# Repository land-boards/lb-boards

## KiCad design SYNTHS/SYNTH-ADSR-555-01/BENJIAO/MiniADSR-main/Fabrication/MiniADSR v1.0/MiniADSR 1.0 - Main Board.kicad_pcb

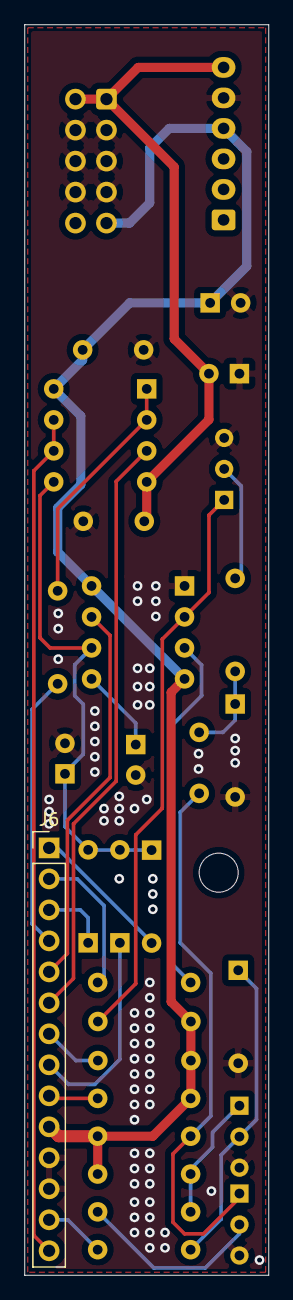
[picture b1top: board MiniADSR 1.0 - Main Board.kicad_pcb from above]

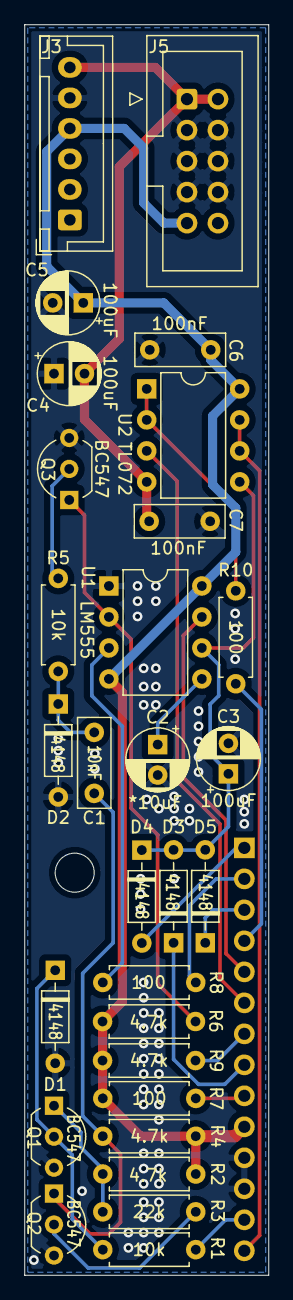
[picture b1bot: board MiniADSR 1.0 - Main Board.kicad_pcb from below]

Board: 2 copper layers, 20.0 x 102.5 mm, 30 parts (29 on the bottom side), 25 nets.

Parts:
C1: 10nF; C_Rect_L7.2mm_W2.5mm_P5.00mm_FKS2_FKP2_MKS2_MKP2
C2: *10uF; CP_Radial_D5.0mm_P2.50mm
C3, C4, C5: 100uF; CP_Radial_D5.0mm_P2.50mm
C6, C7: 100nF; C_Rect_L7.2mm_W2.5mm_P5.00mm_FKS2_FKP2_MKS2_MKP2
D1, D2, D3, D4, D5: 4148; D_DO-35_SOD27_P7.62mm_Horizontal
J3: JST_BUS; JST_XH_B6B-XH-A_1x06_P2.50mm_Vertical
J5: IDC_BUS; IDC-Header_2x05_P2.54mm_Vertical
J6: MainBoard_Pins; PinHeader_1x14_P2.54mm_Vertical
Q1, Q2, Q3: BC547; TO-92_Inline_Wide
R1, R5: 10k; R_Axial_DIN0207_L6.3mm_D2.5mm_P7.62mm_Horizontal
R2, R4, R6, R9: 4.7k; R_Axial_DIN0207_L6.3mm_D2.5mm_P7.62mm_Horizontal
R3: 22k; R_Axial_DIN0207_L6.3mm_D2.5mm_P7.62mm_Horizontal
R7, R8, R10: 100; R_Axial_DIN0207_L6.3mm_D2.5mm_P7.62mm_Horizontal
U1: LM555; DIP-8_W7.62mm
U2: TL072; DIP-8_W7.62mm

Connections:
+12V: C4.1, C6.1, J3.4, J5.9, J5.10, J6.10, R2.2, R4.2, R6.2, R7.1, R9.2, U1.4, U1.8, U2.8
-12V: C5.2, C7.2, J3.6, J5.1, J5.2, U2.4
B1: J6.13, R1.2
B2: J6.14, U2.6, U2.7
B3: D4.2, J6.1
B4: J6.2, R8.2
B5: D5.1, J6.3
B6: J6.4, R10.2
B7: J6.5, U1.7
B8: J6.6, U2.3
B9: J6.7, R9.1
B10: D3.1, J6.8
B11: J6.9, R7.2
GND2: C2.2, C3.2, C4.2, C5.1, C6.2, C7.1, D1.2, D2.2, J3.5, J5.3, J5.4, J5.5, J5.6, J5.7, J5.8, J6.11, J6.12, Q1.3, Q2.3, Q3.3, U1.1
unnamed: C1.1, D2.1, R5.1
unnamed: C1.2, Q2.1, R4.1
unnamed: C2.1, U1.5
unnamed: C3.1, D3.2, D4.1, D5.2, U1.6, U2.5
unnamed: D1.1, Q1.2, R1.1
unnamed: Q1.1, R2.1, R3.1
unnamed: Q2.2, R3.2
unnamed: Q3.1, R6.1, U1.2
unnamed: Q3.2, R5.2
unnamed: R8.1, U1.3
unnamed: R10.1, U2.1, U2.2

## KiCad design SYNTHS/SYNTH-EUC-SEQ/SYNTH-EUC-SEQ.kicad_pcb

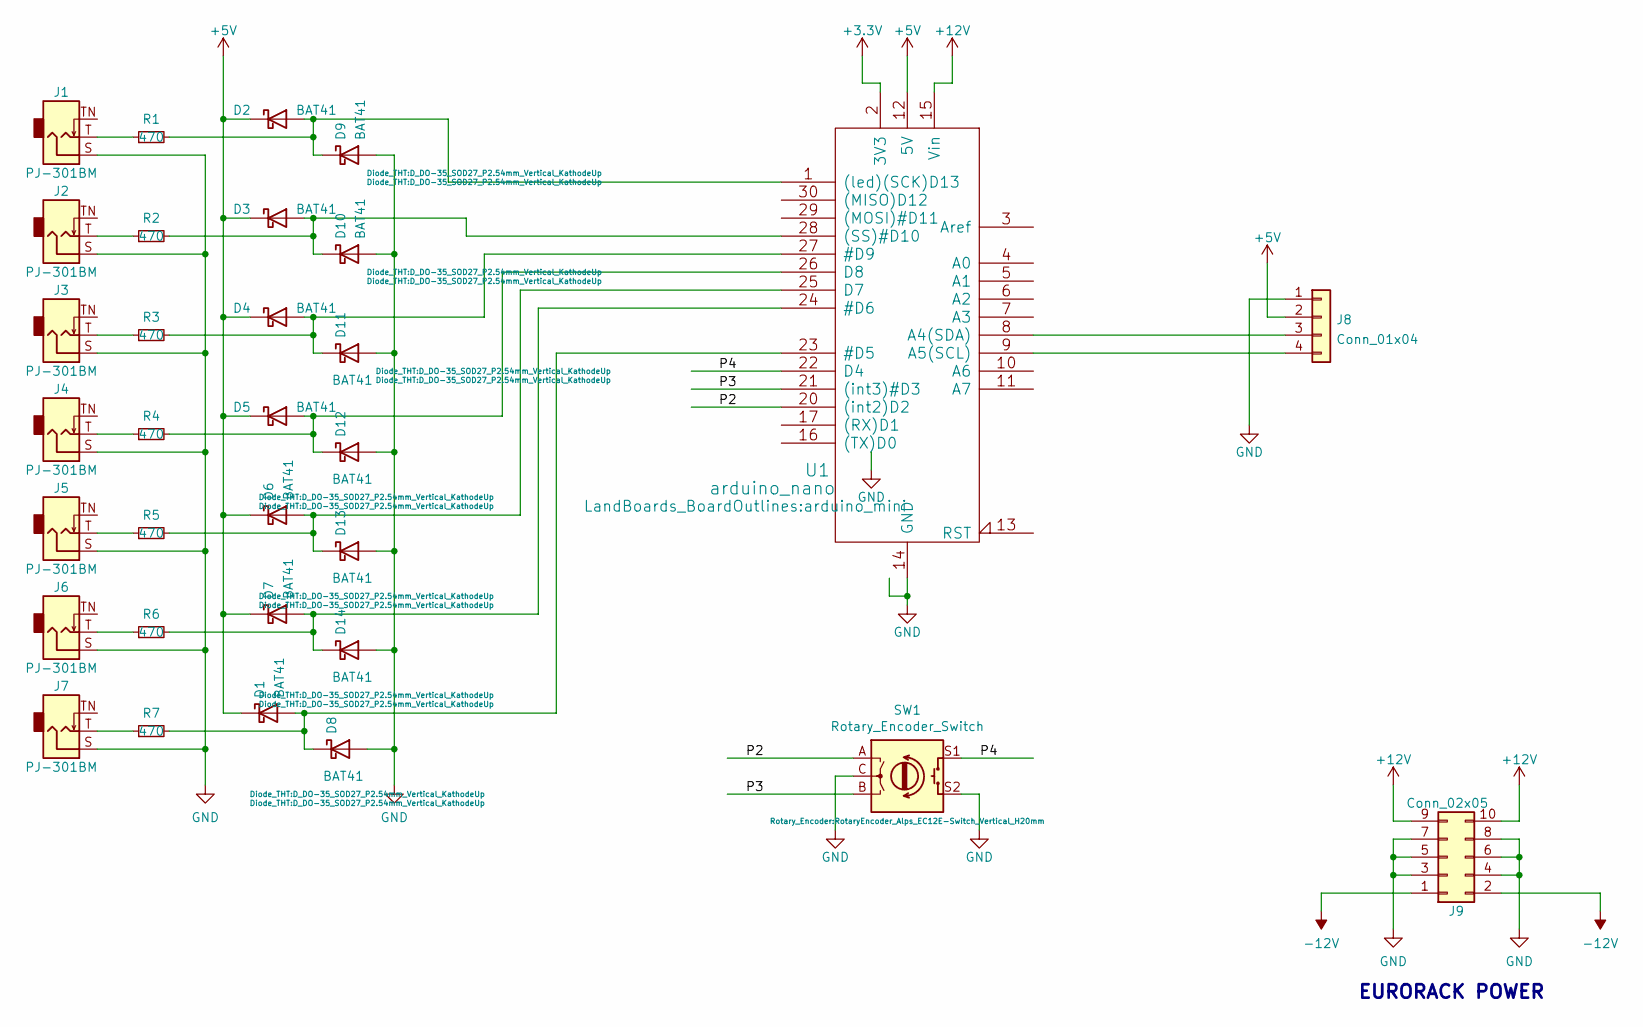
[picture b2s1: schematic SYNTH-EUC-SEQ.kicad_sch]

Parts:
D1, D2, D3, D4, D5, D6, D7, D8, D9, D10, D11, D12, D13, D14: BAT41; D_DO-35_SOD27_P2.54mm_Vertical_KathodeUp
J1, J2, J3, J4, J5, J6, J7: PJ-301BM; Jack_3.5mm_QingPu_WQP-PJ301BM_Vertical
J8: Conn_01x04; PinHeader_1x04_P2.54mm_Vertical
J9: Conn_02x05; IDC-Header_2x05_P2.54mm_Vertical
R1, R2, R3, R4, R5, R6, R7: 470; R_Axial_DIN0204_L3.6mm_D1.6mm_P2.54mm_Vertical
SW1: Rotary_Encoder_Switch; RotaryEncoder_Alps_EC12E-Switch_Vertical_H20mm
U1: arduino_nano; arduino_mini

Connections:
+3V3: U1.2 (3V3)
+5V: D1.1 (K), D2.1 (K), D3.1 (K), D4.1 (K), D5.1 (K), D6.1 (K), D7.1 (K), J8.2, U1.12 (5V)
+12V: J9.9, J9.10, U1.15 (Vin)
-12V: J9.1, J9.2
/P2: SW1.A, U1.20 ((int2)D2)
/P3: SW1.B, U1.21 ((int3)#D3)
/P4: SW1.S1, U1.22 (D4)
GND: D8.2 (A), D9.2 (A), D10.2 (A), D11.2 (A), D12.2 (A), D13.2 (A), D14.2 (A), J1.S, J2.S, J3.S, J4.S, J5.S, J6.S, J7.S, J8.1, J9.3, J9.4, J9.5, J9.6, J9.7, J9.8, SW1.C, SW1.S2, U1.14 (GND), U1.19 (GND)
unnamed: D1.2 (A), D8.1 (K), R7.2, U1.23 (#D5)
unnamed: D2.2 (A), D9.1 (K), R1.2, U1.1 ((led)(SCK)D13)
unnamed: D3.2 (A), D10.1 (K), R2.2, U1.28 ((SS)#D10)
unnamed: D4.2 (A), D11.1 (K), R3.2, U1.27 (#D9)
unnamed: D5.2 (A), D12.1 (K), R4.2, U1.26 (D8)
unnamed: D6.2 (A), D13.1 (K), R5.2, U1.25 (D7)
unnamed: D7.2 (A), D14.1 (K), R6.2, U1.24 (#D6)
unnamed: J1.T, R1.1
unnamed: J2.T, R2.1
unnamed: J3.T, R3.1
unnamed: J4.T, R4.1
unnamed: J5.T, R5.1
unnamed: J6.T, R6.1
unnamed: J7.T, R7.1
unnamed: J8.3, U1.8 (A4(SDA))
unnamed: J8.4, U1.9 (A5(SCL))

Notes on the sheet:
EURORACK POWER

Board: 2 copper layers, 32 parts (1 on the bottom side), 23 nets, no tracks yet.

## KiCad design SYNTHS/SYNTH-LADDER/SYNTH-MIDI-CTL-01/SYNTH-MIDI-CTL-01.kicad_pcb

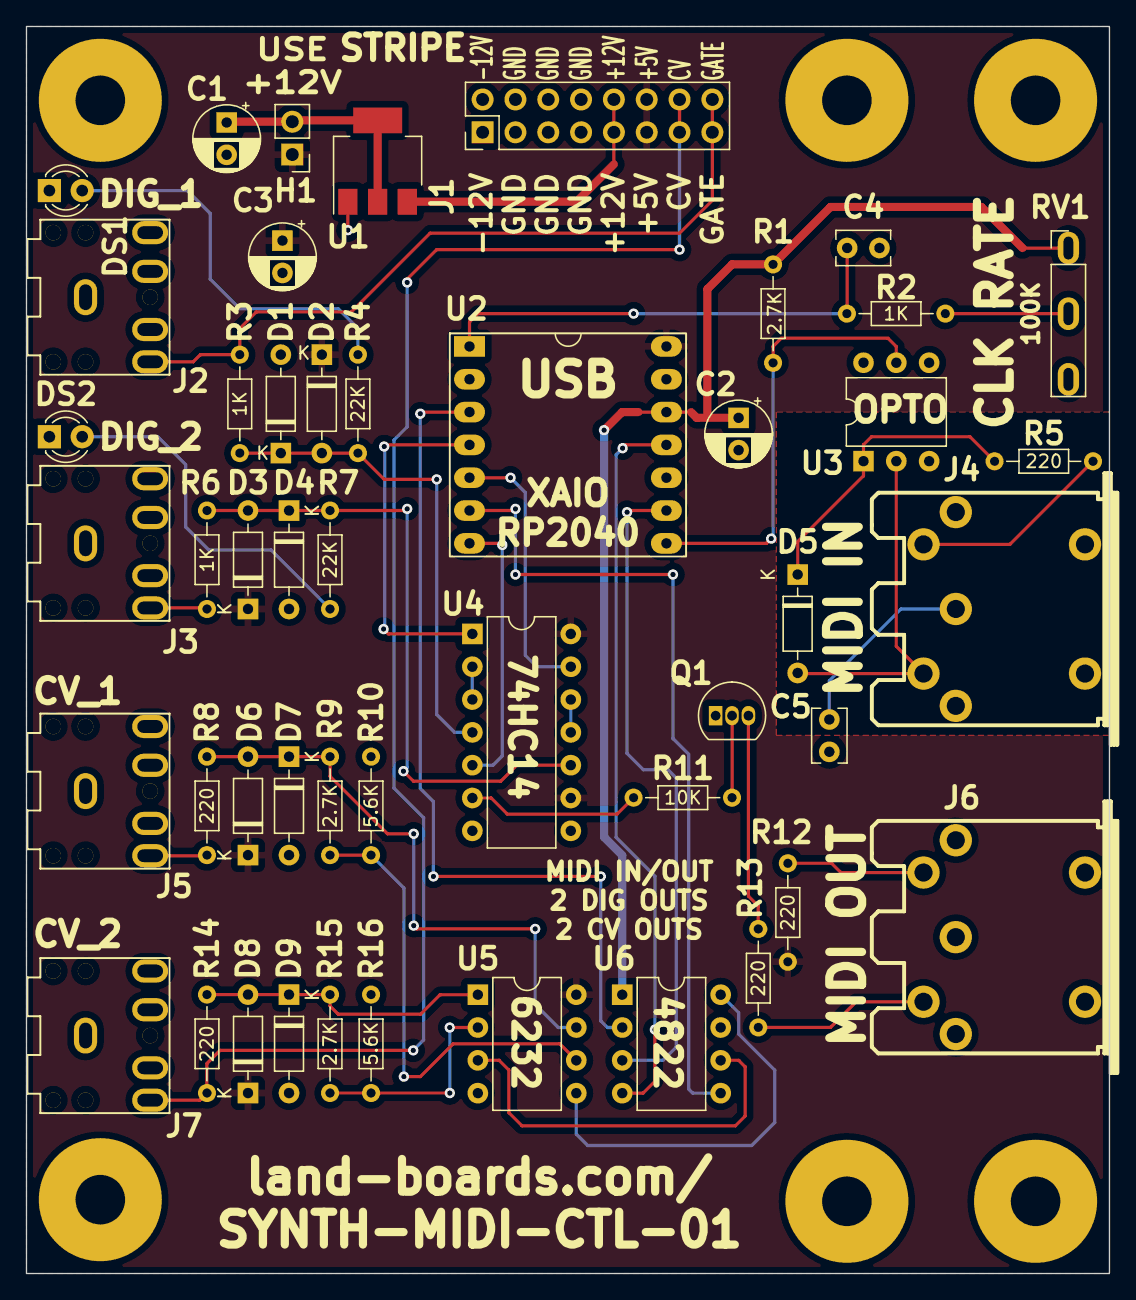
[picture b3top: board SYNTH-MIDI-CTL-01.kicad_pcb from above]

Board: 2 copper layers, 83.8 x 96.5 mm, 54 parts (0 on the bottom side), 40 nets.

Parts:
C1, C2, C3: 47uF; CP_Radial_D5.0mm_P2.50mm
C4: 220pF; C_Rect_L4.0mm_W2.5mm_P2.50mm
C5: 0.1uF; C_Rect_L4.0mm_W2.5mm_P2.50mm
D1, D2, D3, D4, D6, D7, D8, D9: BAT41; D_DO-35_SOD27_P7.62mm_Horizontal
D5: 1N914; D_DO-35_SOD27_P7.62mm_Horizontal
DS1, DS2: LED, 3mm; LED_D3.0mm
H1: HEADER, 1x2; PinHeader_1x02_P2.54mm_Vertical
J1: HEADER, SHRD, 2X8; PinHeader_2x08_P2.54mm_Vertical
J2, J3, J5, J7: AudioJack3; Jack_3.5mm_CUI_SJ1-3523N_Horizontal
J4, J6: DIN-5; MIDI_DIN-5
MTG1, MTG2, MTG3, MTG4, MTG5, MTG6: MountingHole; MTG-6-32
Q1: 2N3904; TO-92_Inline
R1, R9, R15: 2.7K; R_Axial_DIN0204_L3.6mm_D1.6mm_P7.62mm_Horizontal
R2, R3, R6: 1K; R_Axial_DIN0204_L3.6mm_D1.6mm_P7.62mm_Horizontal
R4, R7: 22K; R_Axial_DIN0204_L3.6mm_D1.6mm_P7.62mm_Horizontal
R5, R8, R12, R13, R14: 220; R_Axial_DIN0204_L3.6mm_D1.6mm_P7.62mm_Horizontal
R10, R16: 5.6K; R_Axial_DIN0204_L3.6mm_D1.6mm_P7.62mm_Horizontal
R11: 10K; R_Axial_DIN0204_L3.6mm_D1.6mm_P7.62mm_Horizontal
RV1: 100K; Pot3
U1: AZ1117H-5; SOT-223
U2: XIAO_RP2040; QT_Py
U3: CNY17-4X006; DIP-6_W7.62mm
U4: 74HC14; DIP-14_W7.62mm
U5: MCP6232; DIP-8_W7.62mm
U6: MCP4822-E/P; DIP-8_W7.62mm

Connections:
+3V3: C2.1, R1.2, RV1.1, U2.12 (3.3V), U6.1 (Vdd)
+5V: C3.1, D2.1 (K), D3.1 (K), D6.1 (K), D8.1 (K), H1.1, J1.11, J1.12, R12.2, U2.14 (5V), U4.9, U4.14 (VCC), U5.8 (VDD)
+12V: J1.9, J1.10, U1.3 (VIN)
/CLK: U2.5 (D4/SDA/P6), U4.13
/CLK_I: D3.2 (A), D4.1 (K), R6.1, R7.2, U4.10
/CV1: J5.T, R8.2
/CV2: J1.13, J1.14, J7.T, R14.2
/DIG1: J1.15, J1.16, J2.T, R3.2
/DIG2: J3.T, R6.2
/FREQ_POT: C4.1, R2.2, U2.1 (D0/P26)
/GATE: U2.4 (D3/P29), U4.1
/GATE_I: D1.1 (K), D2.2 (A), R3.1, R4.2, U4.4
/MIDI_IN: J4.4, R5.1
/RXD: R1.1, U2.8 (D7/RX/P1), U3.5
/SPI_LDAC: U2.6 (D5/SCL/P7), U6.5 (~LDAC)
/SPI_MOSI: U2.11 (D10/MOSI/P3), U6.4 (SDI)
/SPI_SCK: U2.9 (D8/SCK/P2), U6.3 (SCK)
/SPI_SS: U2.3 (D2/P28), U6.2 (~CS)
/TXD: U2.7 (D6/TX/P0), U4.5
GND: C1.2, C2.2, C3.2, C4.2, C5.2, D1.2 (A), D4.2 (A), D7.2 (A), D9.2 (A), DS1.1 (K), DS2.1 (K), J1.3, J1.4, J1.5, J1.6, J1.7, J1.8, J2.S, J3.S, J5.S, J6.2, J7.S, Q1.1 (E), R10.1, R16.1, RV1.3, U1.1 (GND), U2.13 (GND), U3.4, U4.7 (GND), U5.4 (VSS), U6.7 (Vss)
unnamed: C1.1, H1.2, U1.2 (VO), U1.4 (VO)
unnamed: C5.1, J4.2
unnamed: D5.1 (K), R5.2, U3.1
unnamed: D5.2 (A), J4.5, U3.2
unnamed: D6.2 (A), D7.1 (K), R8.1, R9.2, U5.7 (Q)
unnamed: D8.2 (A), D9.1 (K), R14.1, R15.2, U5.1 (Q)
unnamed: DS1.2 (A), R4.1
unnamed: DS2.2 (A), R7.1
unnamed: J6.4, R12.1
unnamed: J6.5, R13.2
unnamed: Q1.2 (B), R11.1
unnamed: Q1.3 (C), R13.1
unnamed: R2.1, RV1.2
unnamed: R9.1, R10.2, U5.6 (-)
unnamed: R11.2, U4.6
unnamed: R15.1, R16.2, U5.2 (-)
unnamed: U4.2, U4.3
unnamed: U4.11, U4.12
unnamed: U5.3 (+), U6.6 (VB)
unnamed: U5.5 (+), U6.8 (VA)

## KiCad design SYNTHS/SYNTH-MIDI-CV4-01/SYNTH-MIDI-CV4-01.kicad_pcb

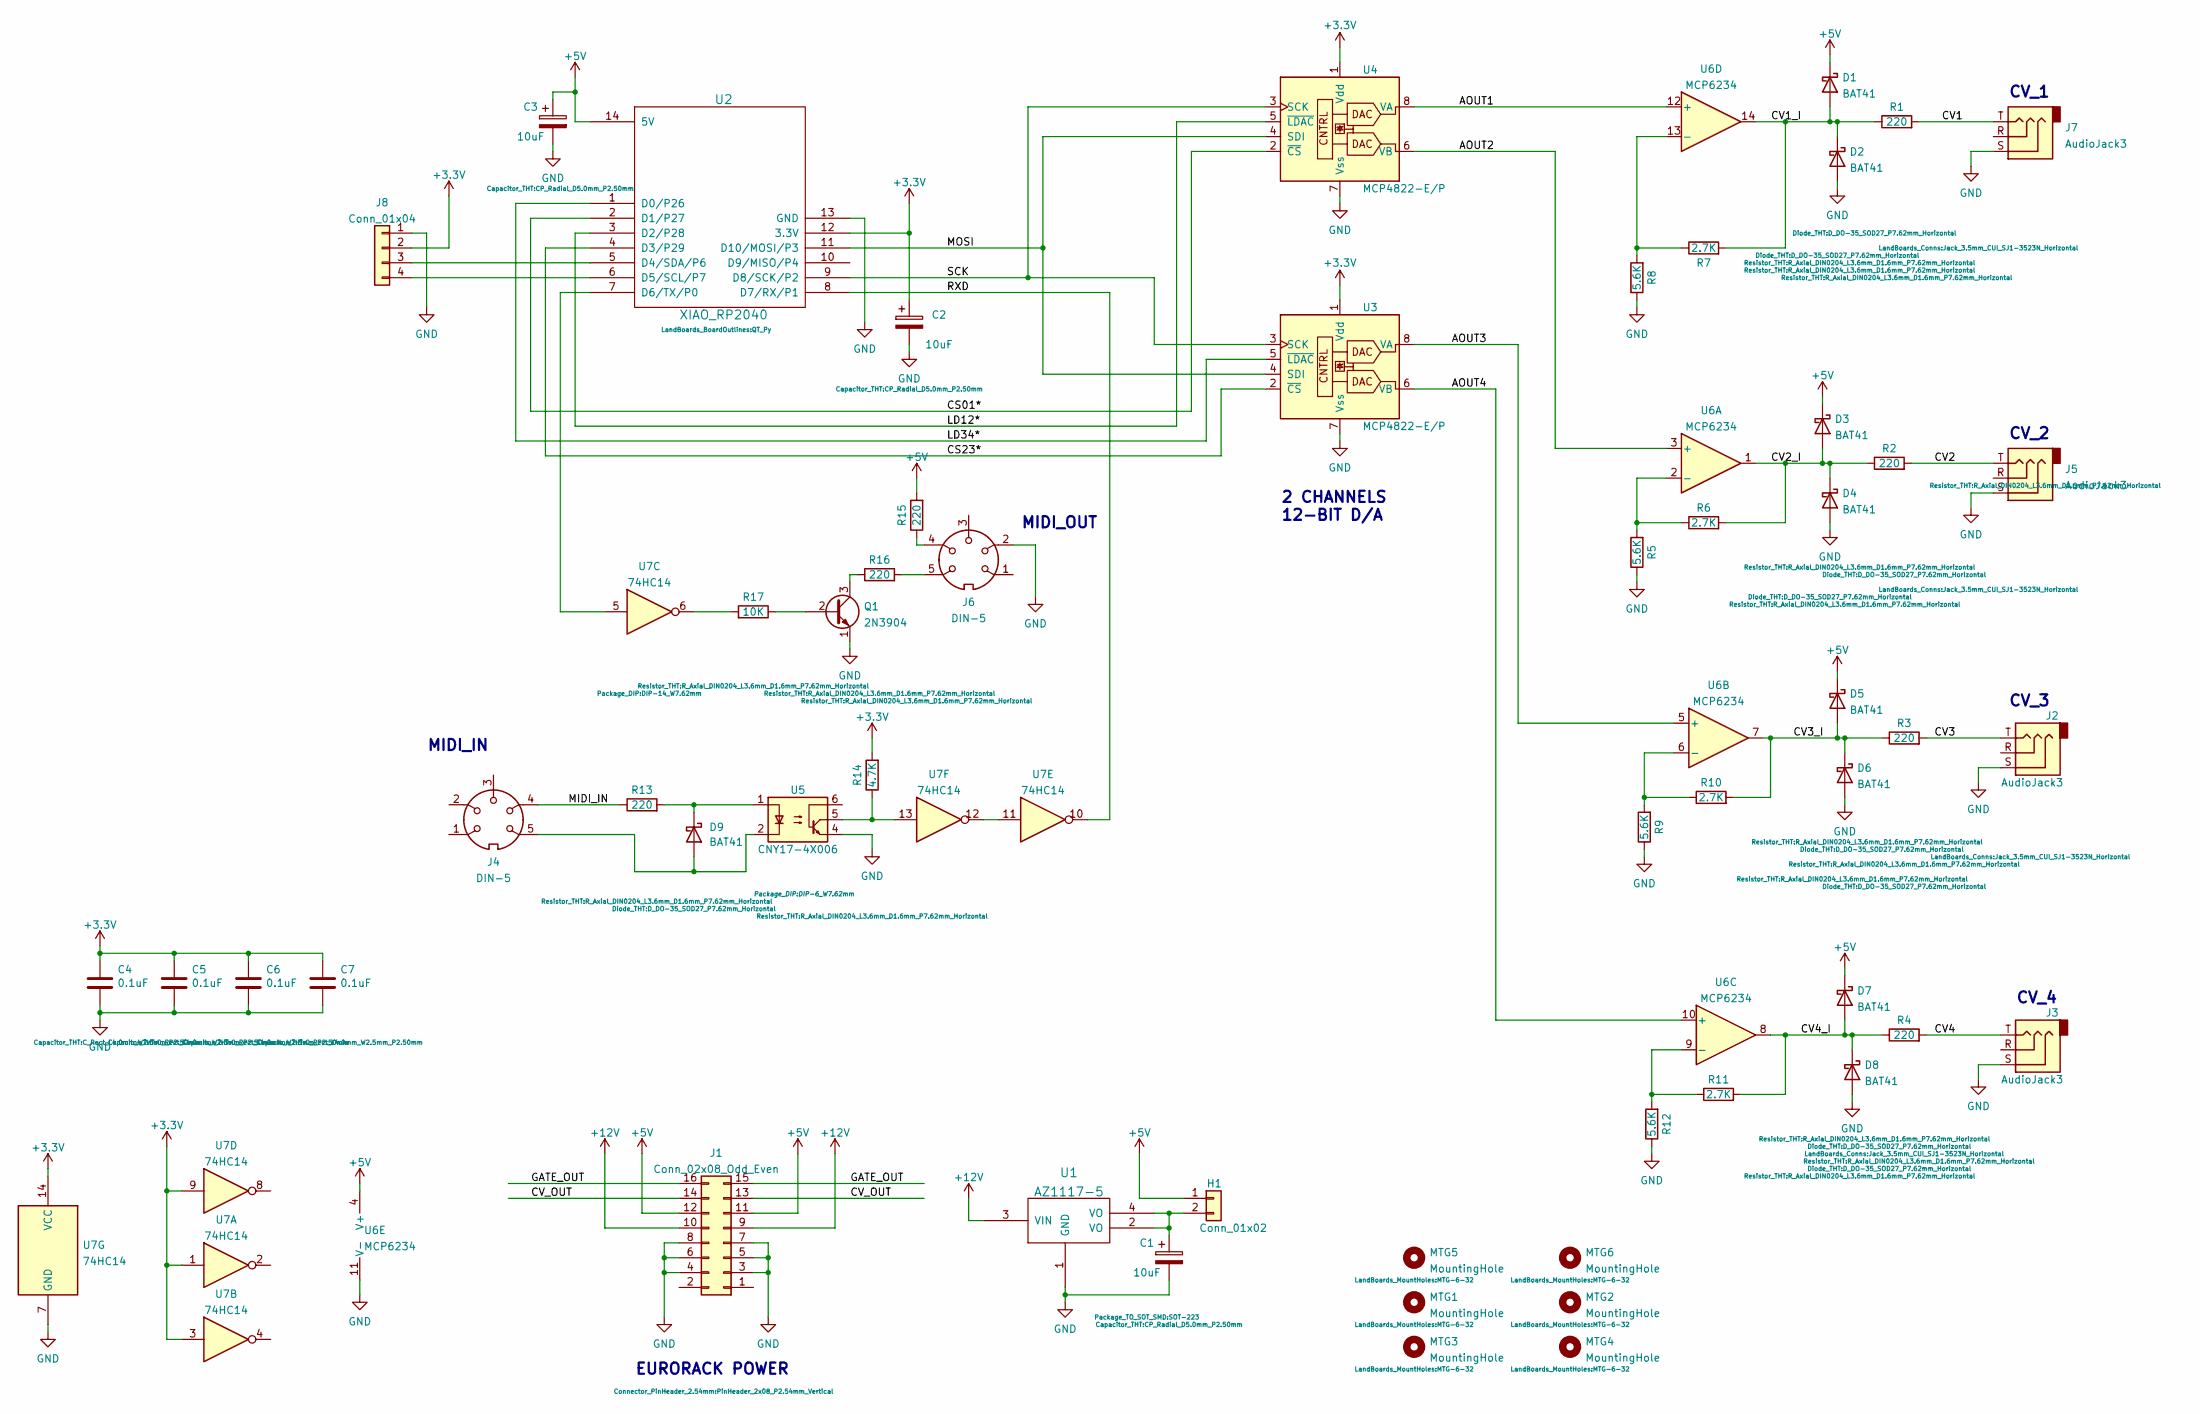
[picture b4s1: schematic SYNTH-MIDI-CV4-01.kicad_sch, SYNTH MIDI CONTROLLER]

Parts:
C1, C2, C3: 10uF; CP_Radial_D5.0mm_P2.50mm
C4, C5, C6, C7: 0.1uF; C_Rect_L4.0mm_W2.5mm_P2.50mm
D1, D2, D3, D4, D5, D6, D7, D8, D9: BAT41; D_DO-35_SOD27_P7.62mm_Horizontal
H1: Conn_01x02; PinHeader_1x02_P2.54mm_Vertical
J1: Conn_02x08_Odd_Even; PinHeader_2x08_P2.54mm_Vertical
J2, J3, J5, J7: AudioJack3; Jack_3.5mm_CUI_SJ1-3523N_Horizontal
J4, J6: DIN-5; MIDI_DIN-5
J8: Conn_01x04
MTG1, MTG2, MTG3, MTG4, MTG5, MTG6: MountingHole; MTG-6-32
Q1: 2N3904; TO-92_Inline
R1, R2, R3, R4, R13, R15, R16: 220; R_Axial_DIN0204_L3.6mm_D1.6mm_P7.62mm_Horizontal
R5, R8, R9, R12: 5.6K; R_Axial_DIN0204_L3.6mm_D1.6mm_P7.62mm_Horizontal
R6, R7, R10, R11: 2.7K; R_Axial_DIN0204_L3.6mm_D1.6mm_P7.62mm_Horizontal
R14: 4.7K; R_Axial_DIN0204_L3.6mm_D1.6mm_P7.62mm_Horizontal
R17: 10K; R_Axial_DIN0204_L3.6mm_D1.6mm_P7.62mm_Horizontal
U1: AZ1117-5; SOT-223
U2: XIAO_RP2040; QT_Py
U3, U4: MCP4822-E/P; DIP-8_W7.62mm
U5: CNY17-4X006; DIP-6_W7.62mm
U6: MCP6234; DIP-14_W7.62mm
U7: 74HC14; DIP-14_W7.62mm

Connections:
+3V3: C2.1, C4.1, C5.1, C6.1, C7.1, J8.2, R14.2, U2.12 (3.3V), U3.1 (Vdd), U4.1 (Vdd), U7.1, U7.3, U7.9, U7.14 (VCC)
+5V: C3.1, D1.1 (K), D3.1 (K), D5.1 (K), D7.1 (K), H1.1, J1.11, J1.12, R15.2, U2.14 (5V), U6.4 (V+)
+12V: J1.9, J1.10, U1.3 (VIN)
/AOUT1: U4.8 (VA), U6.12 (+)
/AOUT2: U4.6 (VB), U6.3 (+)
/AOUT3: U3.8 (VA), U6.5 (+)
/AOUT4: U3.6 (VB), U6.10 (+)
/CS01*: U2.2 (D1/P27), U4.2 (~CS)
/CS23*: U2.4 (D3/P29), U3.2 (~CS)
/CV1: J7.T, R1.2
/CV1_I: D1.2 (A), D2.1 (K), R1.1, R7.2, U6.14
/CV2: J5.T, R2.2
/CV2_I: D3.2 (A), D4.1 (K), R2.1, R6.2, U6.1
/CV3: J2.T, R3.2
/CV3_I: D5.2 (A), D6.1 (K), R3.1, R10.2, U6.7
/CV4: J3.T, R4.2
/CV4_I: D7.2 (A), D8.1 (K), R4.1, R11.2, U6.8
/CV_OUT: J1.13, J1.14
/GATE_OUT: J1.15, J1.16
/LD12*: U2.3 (D2/P28), U4.5 (~LDAC)
/LD34*: U2.1 (D0/P26), U3.5 (~LDAC)
/MIDI_IN: J4.4, R13.1
/MOSI: U2.11 (D10/MOSI/P3), U3.4 (SDI), U4.4 (SDI)
/RXD: U2.8 (D7/RX/P1), U7.10
/SCK: U2.9 (D8/SCK/P2), U3.3 (SCK), U4.3 (SCK)
GND: C1.2, C2.2, C3.2, C4.2, C5.2, C6.2, C7.2, D2.2 (A), D4.2 (A), D6.2 (A), D8.2 (A), J1.3, J1.4, J1.5, J1.6, J1.7, J1.8, J2.S, J3.S, J5.S, J6.2, J7.S, J8.1, Q1.1 (E), R5.1, R8.1, R9.1, R12.1, U1.1 (GND), U2.13 (GND), U3.7 (Vss), U4.7 (Vss), U5.4, U6.11 (V-), U7.7 (GND)
unnamed: C1.1, H1.2, U1.2 (VO), U1.4 (VO)
unnamed: D9.1 (K), R13.2, U5.1
unnamed: D9.2 (A), J4.5, U5.2
unnamed: J6.4, R15.1
unnamed: J6.5, R16.2
unnamed: J8.3, U2.5 (D4/SDA/P6)
unnamed: J8.4, U2.6 (D5/SCL/P7)
unnamed: Q1.2 (B), R17.1
unnamed: Q1.3 (C), R16.1
unnamed: R5.2, R6.1, U6.2 (-)
unnamed: R7.1, R8.2, U6.13 (-)
unnamed: R9.2, R10.1, U6.6 (-)
unnamed: R11.1, R12.2, U6.9 (-)
unnamed: R14.1, U5.5, U7.13
unnamed: R17.2, U7.6
unnamed: U2.7 (D6/TX/P0), U7.5
unnamed: U7.11, U7.12

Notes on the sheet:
CV_1
CV_3
MIDI_IN
2 CHANNELS 12-BIT D/A
MIDI_OUT
CV_4
CV_2
EURORACK POWER

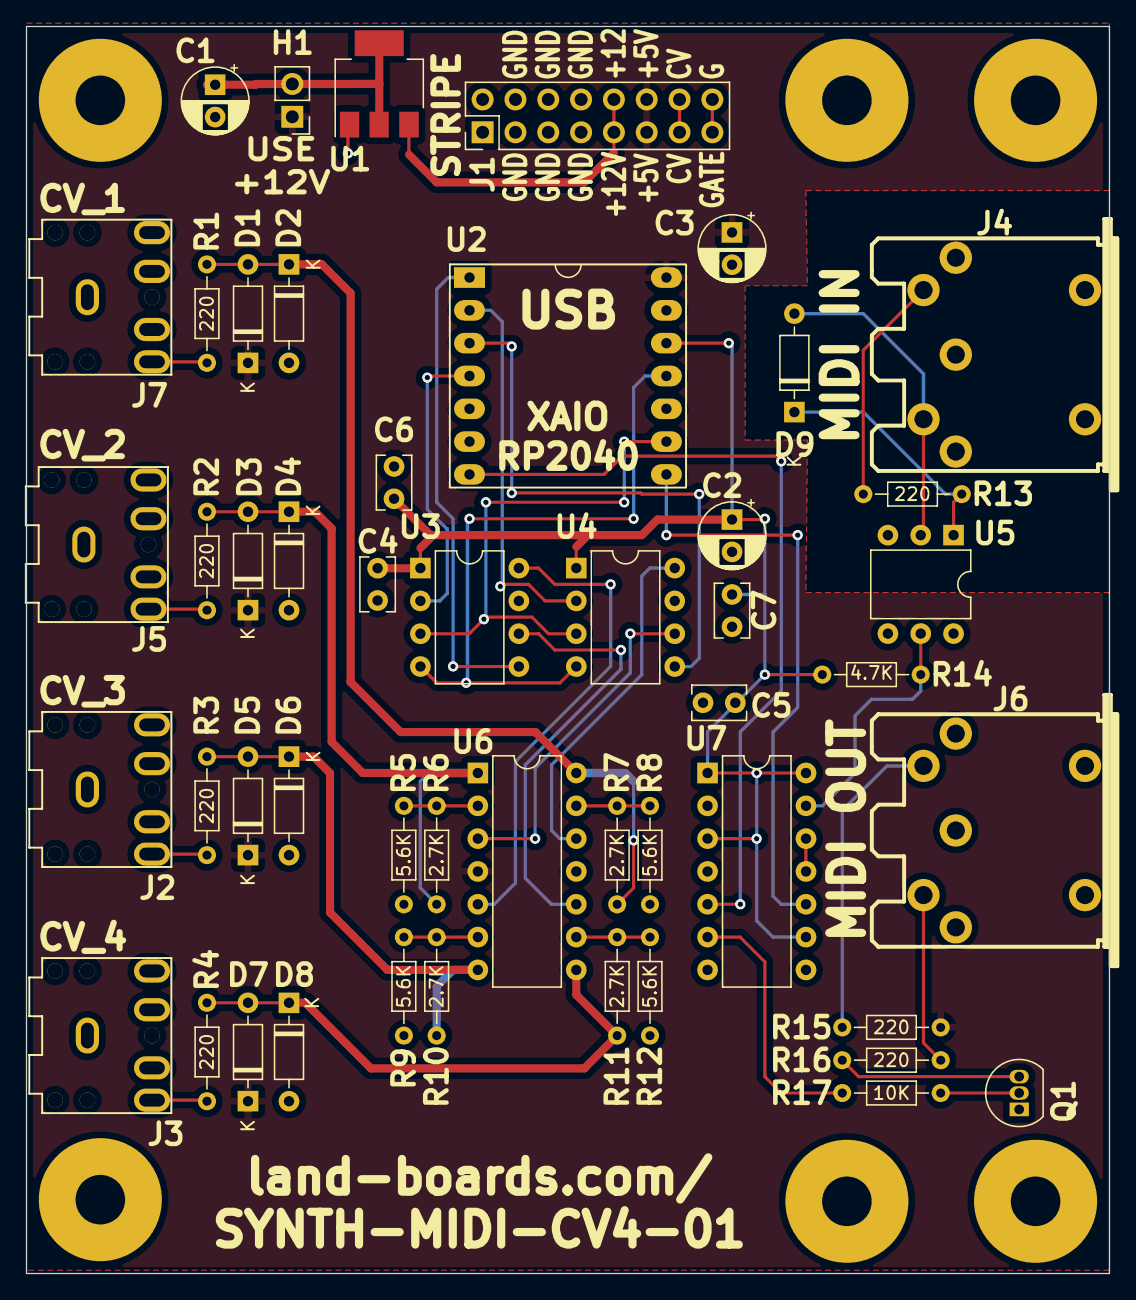
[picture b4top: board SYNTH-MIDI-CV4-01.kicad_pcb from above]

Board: 2 copper layers, 83.8 x 96.5 mm, 55 parts (0 on the bottom side), 41 nets.
